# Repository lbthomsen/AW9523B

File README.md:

# AW9523B
AW9523B GPIO Expander Breakout Board and Library

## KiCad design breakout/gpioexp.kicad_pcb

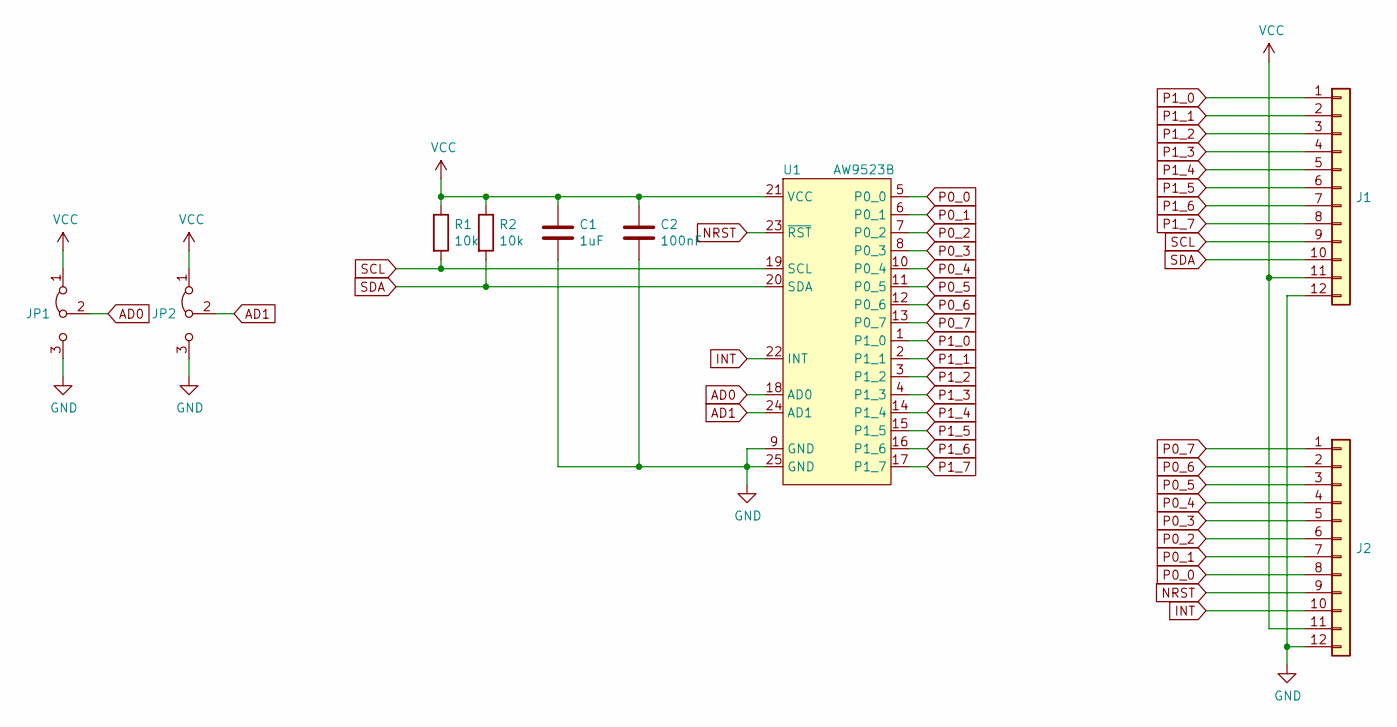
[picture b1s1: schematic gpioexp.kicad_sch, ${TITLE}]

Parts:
C1: 1uF; C_0603_1608Metric; LCSC C15849
C2: 100nF; C_0603_1608Metric; LCSC C14663
J1, J2: PinHeader_1x12_P2.54mm_Vertical
JP1, JP2: SolderJumper-3_P1.3mm_Bridged2Bar12_Pad1.0x1.5mm
R1, R2: 10k; R_0603_1608Metric; LCSC C25804
U1: AW9523B; QFN-24-1EP_4x4mm_P0.5mm_EP2.6x2.6mm; LCSC C148077

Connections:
AD0: JP1.2 (C), U1.18 (AD0)
AD1: JP2.2 (C), U1.24 (AD1)
GND: C1.2, C2.2, J1.12, J2.12, JP1.3 (B), JP2.3 (B), U1.9 (GND), U1.25 (GND)
INT: J2.10, U1.22 (INT)
NRST: J2.9, U1.23 (~RST)
P0_0: J2.8, U1.5 (P0_0)
P0_1: J2.7, U1.6 (P0_1)
P0_2: J2.6, U1.7 (P0_2)
P0_3: J2.5, U1.8 (P0_3)
P0_4: J2.4, U1.10 (P0_4)
P0_5: J2.3, U1.11 (P0_5)
P0_6: J2.2, U1.12 (P0_6)
P0_7: J2.1, U1.13 (P0_7)
P1_0: J1.1, U1.1 (P1_0)
P1_1: J1.2, U1.2 (P1_1)
P1_2: J1.3, U1.3 (P1_2)
P1_3: J1.4, U1.4 (P1_3)
P1_4: J1.5, U1.14 (P1_4)
P1_5: J1.6, U1.15 (P1_5)
P1_6: J1.7, U1.16 (P1_6)
P1_7: J1.8, U1.17 (P1_7)
SCL: J1.9, R1.2, U1.19 (SCL)
SDA: J1.10, R2.2, U1.20 (SDA)
VCC: C1.1, C2.1, J1.11, J2.11, JP1.1 (A), JP2.1 (A), R1.1, R2.1, U1.21 (VCC)

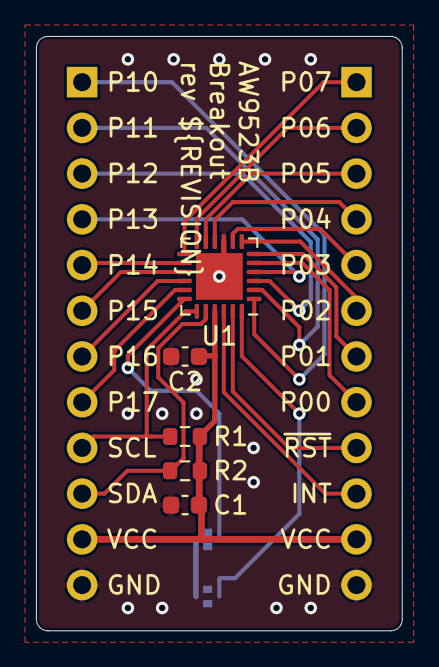
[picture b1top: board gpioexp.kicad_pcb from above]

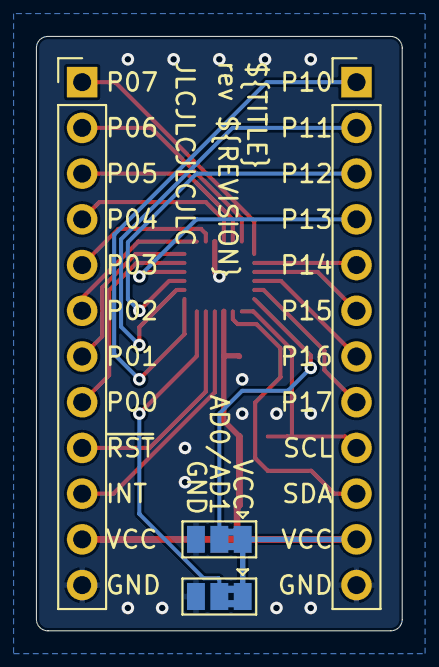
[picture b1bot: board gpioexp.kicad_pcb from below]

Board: 2 copper layers, 20.3 x 33.0 mm, 9 parts (4 on the bottom side), 24 nets.

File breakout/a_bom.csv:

Comment,Designator,Footprint,LCSC, LCSC
"100nF","C1","Capacitor_SMD:C_0603_1608Metric","","C14663"
"~","J1,J2","Connector_PinHeader_2.54mm:PinHeader_1x12_P2.54mm_Vertical",""
"~","JP1,JP2","Jumper:SolderJumper-3_P1.3mm_Bridged2Bar12_Pad1.0x1.5mm",""
"10k","R1,R2","Resistor_SMD:R_0603_1608Metric","","C25804"
"AW9523BTQR","U1","Package_DFN_QFN:WQFN-24-1EP_4x4mm_P0.5mm_EP2.6x2.6mm","","C148077"

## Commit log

2022-04-26 Added datasheet
2022-04-26 Hmmmm
2022-04-28 Updated PCB
2022-04-30 Rev c should be ready
